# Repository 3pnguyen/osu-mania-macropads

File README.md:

# osu-mania-macropads 

## A repository that combines two seperate projects of similar design intentions but different executions.

<div align="center">
    <table>
        <tr>
            <td></td>
            <td></td>
        </tr>
    </table>
</div>

## ✨ About

At the start of the summer of 26' and as an osu! mania player, I started to develop a specialized macropad/keypad to play the game. Thinking of it as a quick and minimalistic project, that was the way I designed it. Minimalistic as in straight-up only a microcontroller and switches slapped onto a PCB. With only a total of 3 days working time, I finished it and thought it would be the end. But, my friend discovering the project, asked me to make a more "hardcore" version. Compared to the first version, we're talking about a potential of 9K mania, hall-effect switches, rapid trigger, etc. Orignally for the initial version, this repository has been repurposed to hold both. These two are brothers in arms, designed for different people with different demands but no less can be compiled together.

## 🖼️ Gallery

<div align="center">
    <table>
        <tr>
            <td></td>
            <td></td>
        </tr>
        <tr>
            <td></td>
            <td></td>
        </tr>
    </table>
</div>

<div align="center">
    <table>
        <tr>
            <td></td>
            <td></td>
        </tr>
    </table>
</div>

<div align="center">
    <table>
        <tr>
            <td></td>
            <td></td>
        </tr>
    </table>
</div>

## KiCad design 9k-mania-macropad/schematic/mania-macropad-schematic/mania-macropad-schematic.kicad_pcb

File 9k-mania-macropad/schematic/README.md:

# Schematic

<div align="center">

</div>

## Parts List

* [0.1uf](https://www.mouser.com/en/ProductDetail/KEMET/C322C104K5R5TA?qs=XvIqZs20p47gvrtGJkxvnw%3D%3D&srsltid=AfmBOoqY4KrbQpnZ-huLh4W_OdS7XR-RYfdhxsaF2TdTgfn78qcFuNxP)
* [10uf](https://www.mouser.com/en/ProductDetail/KEMET/C320C106K3R5TA?qs=uSb533yqMR%252BI5DZ88AMWgA%3D%3D&srsltid=AfmBOorKWxTFM7sGESwl3Y5iid5M9OMpDOqWwjicTUXBzjN7W4jSN1yL)
* [3.3k](https://www.mouser.com/en/ProductDetail/Vishay-Dale/RN55C3301FB14?qs=S3NOsHn6j1POW9KhX3p6iw%3D%3D)
* [4.7k](https://www.mouser.com/en/ProductDetail/Vishay-Dale/RN55C4701FB14?qs=iv4S7zUmpfIvlpqX3oroLw%3D%3D)
* [A1324LLHLT-T (Hall effect SOT-23-3)](https://www.mouser.com/en/ProductDetail/Allegro-MicroSystems/A1324LLHLT-T?qs=pUKx8fyJudDKEne7imXs%252BA%3D%3D)
* [971050321 (M3 5mm M-F Standoff)](https://www.mouser.com/en/ProductDetail/Wurth-Elektronik/971050321?qs=wr8lucFkNMVovcsNMvdJcg%3D%3D)|
* [M3 Screw](https://www.mouser.com/en/ProductDetail/APM-HEXSEAL/SM3X6MM-2701?qs=EY%2FnVpK1mpyaLaNu%2BOcvfQ%3D%3D)
* [M3 Nut](https://www.mouser.com/en/ProductDetail/Harwin/KA1-4300000?qs=HoCaDK9Nz5fHqS%2FcIXdxOA%3D%3D)
* [Teensy 4.0](https://www.mouser.com/en/ProductDetail/SparkFun/DEV-16997?qs=hWgE7mdIu5T2C4RvZCDz%2FQ%3D%3D)
* 6mm Push button - from local electronics store
* D5mm LED - from a random Arduino starter kit

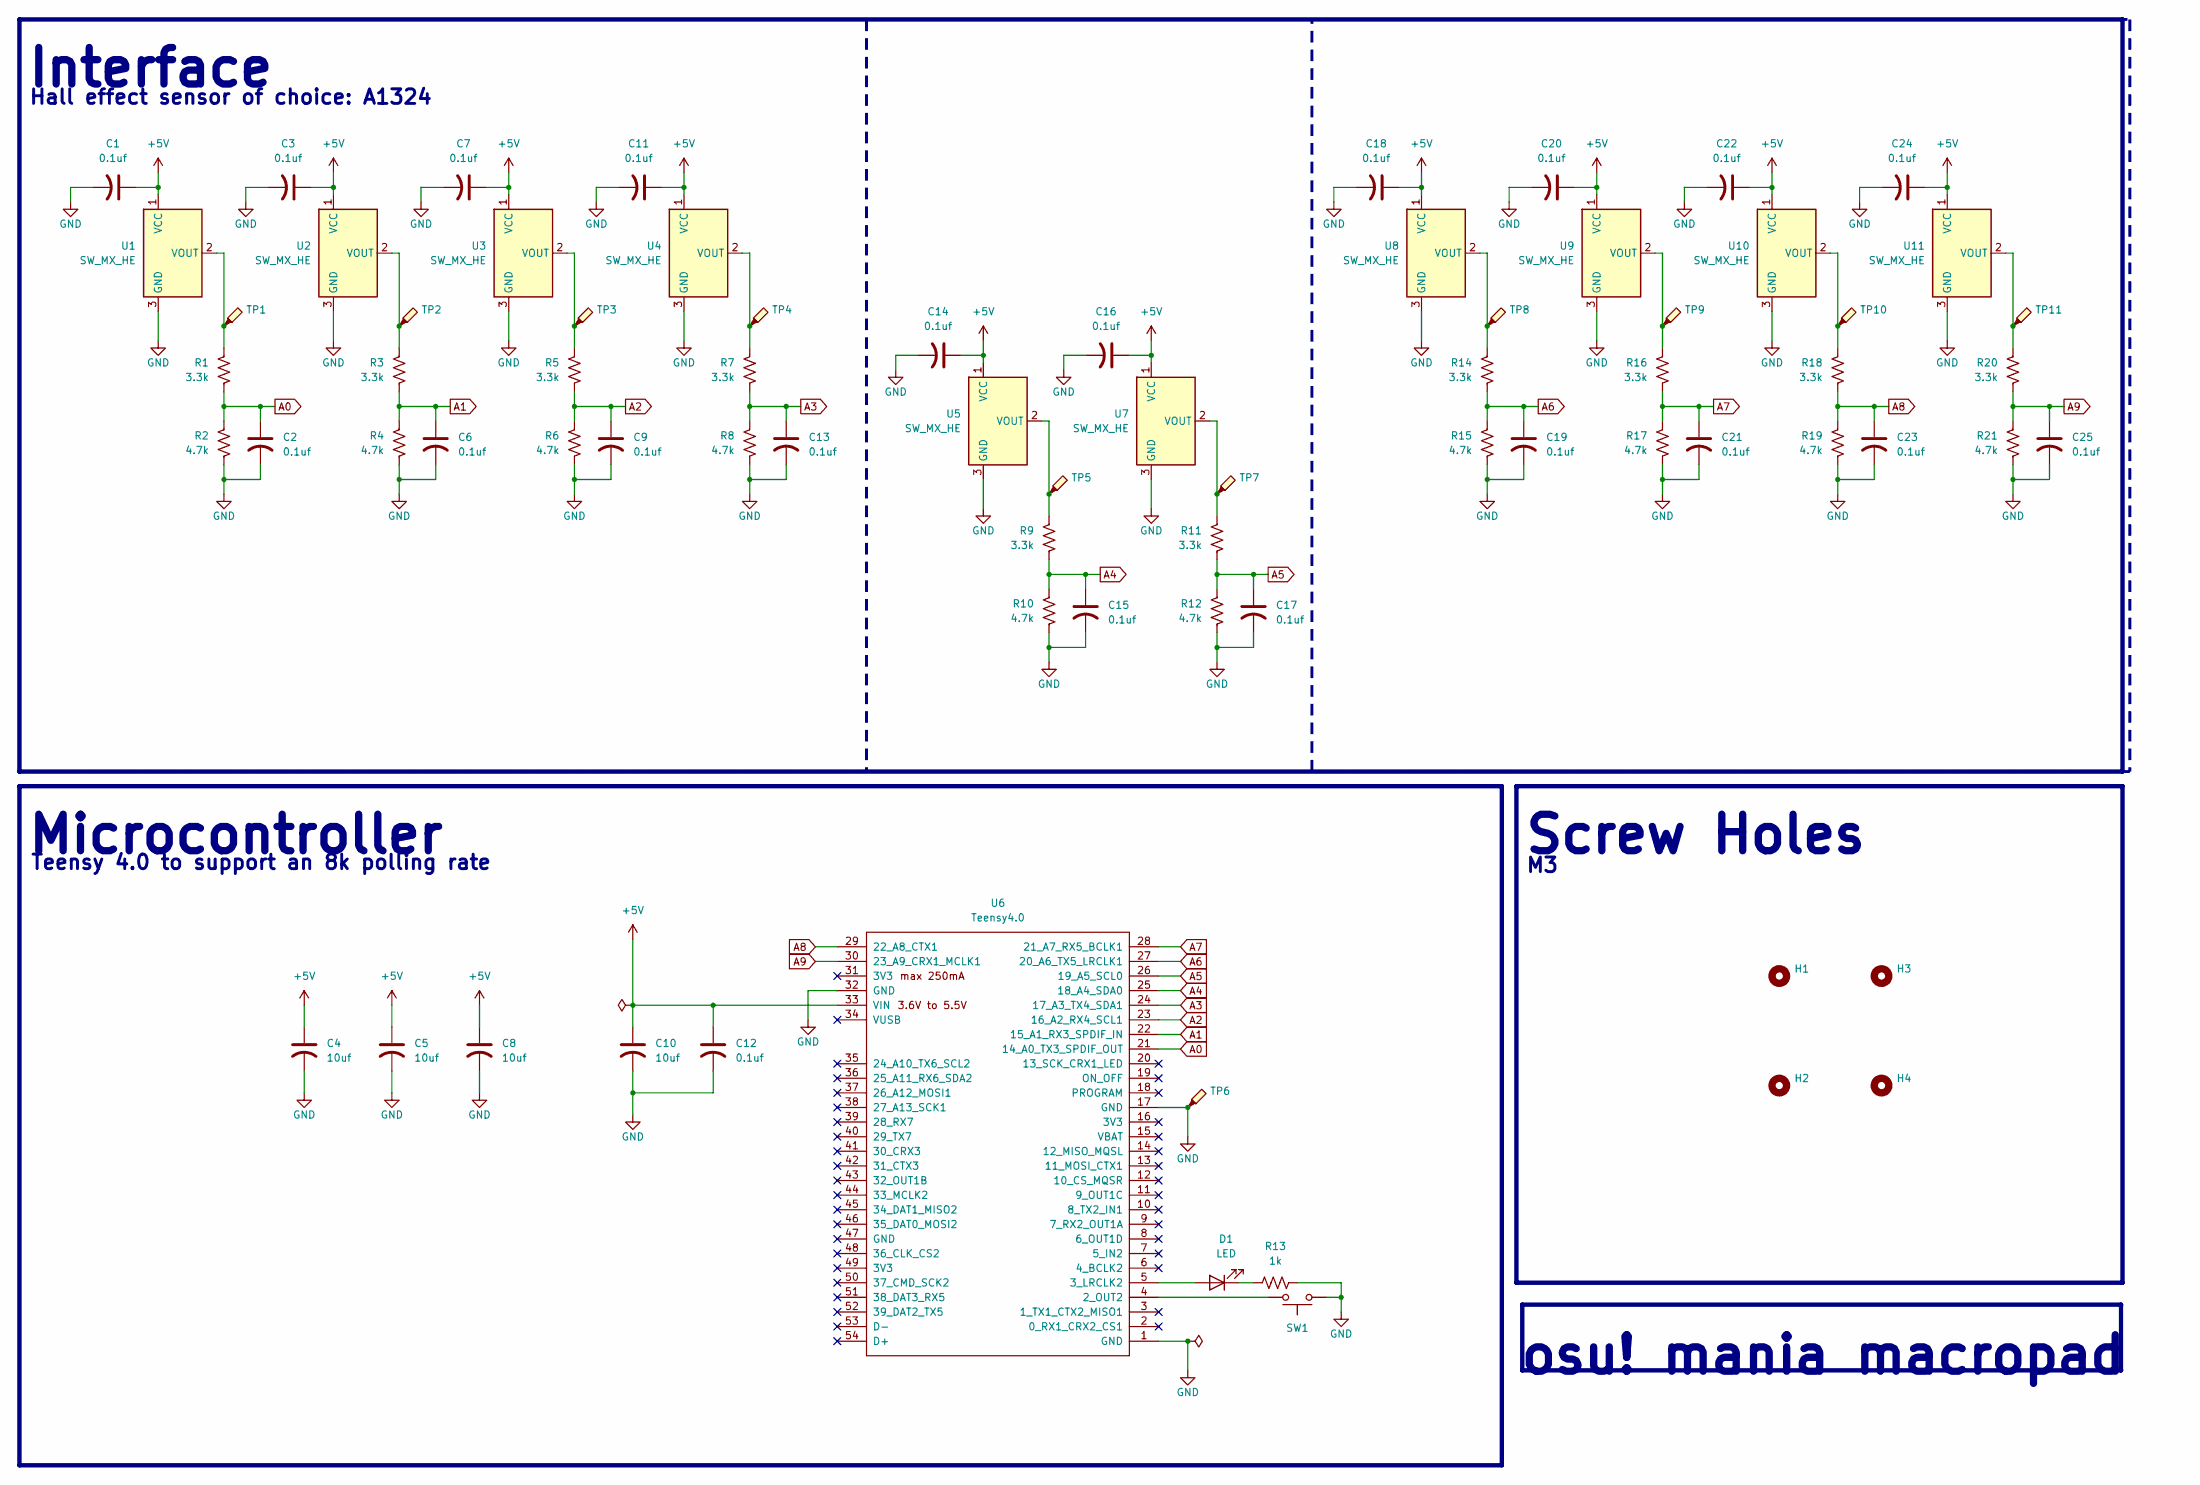
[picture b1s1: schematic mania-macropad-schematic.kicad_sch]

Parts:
C1, C2, C3, C6, C7, C9, C11, C12, C13, C14, C15, C16, C17, C18, C19, C20, C21, C22, C23, C24, C25: 0.1uf; C_Disc_D5.1mm_W3.2mm_P5.00mm
C4, C5, C8, C10: 10uf; C_Disc_D5.0mm_W2.5mm_P2.50mm
D1: LED; LED_D5.0mm
H1, H2, H3, H4: MountingHole; MountingHole_3.2mm_M3
R1, R3, R5, R7, R9, R11, R14, R16, R18, R20: 3.3k; R_Axial_DIN0207_L6.3mm_D2.5mm_P10.16mm_Horizontal
R2, R4, R6, R8, R10, R12, R15, R17, R19, R21: 4.7k; R_Axial_DIN0207_L6.3mm_D2.5mm_P10.16mm_Horizontal
R13: 1k; R_Axial_DIN0309_L9.0mm_D3.2mm_P12.70mm_Horizontal
SW1: SW_Push; SW_PUSH_6mm_H7.3mm
TP1, TP2, TP3, TP4, TP5, TP6, TP7, TP8, TP9, TP10, TP11: TestPoint_Probe; TestPoint_Pad_D1.5mm
U1, U2, U3, U4, U5, U7, U8, U9, U10, U11: SW_MX_HE; SW_MX_HE_0deg_1u
U6: Teensy4.0; Teensy40

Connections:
+5V: C1.1, C3.1, C4.1, C5.1, C7.1, C8.1, C10.1, C11.1, C12.1, C14.1, C16.1, C18.1, C20.1, C22.1, C24.1, U1.1 (VCC), U2.1 (VCC), U3.1 (VCC), U4.1 (VCC), U5.1 (VCC), U6.33 (VIN), U7.1 (VCC), U8.1 (VCC), U9.1 (VCC), U10.1 (VCC), U11.1 (VCC)
A0: C2.1, R1.2, R2.1, U6.21 (14_A0_TX3_SPDIF_OUT)
A1: C6.1, R3.2, R4.1, U6.22 (15_A1_RX3_SPDIF_IN)
A2: C9.1, R5.2, R6.1, U6.23 (16_A2_RX4_SCL1)
A3: C13.1, R7.2, R8.1, U6.24 (17_A3_TX4_SDA1)
A4: C15.1, R9.2, R10.1, U6.25 (18_A4_SDA0)
A5: C17.1, R11.2, R12.1, U6.26 (19_A5_SCL0)
A6: C19.1, R14.2, R15.1, U6.27 (20_A6_TX5_LRCLK1)
A7: C21.1, R16.2, R17.1, U6.28 (21_A7_RX5_BCLK1)
A8: C23.1, R18.2, R19.1, U6.29 (22_A8_CTX1)
A9: C25.1, R20.2, R21.1, U6.30 (23_A9_CRX1_MCLK1)
GND: C1.2, C2.2, C3.2, C4.2, C5.2, C6.2, C7.2, C8.2, C9.2, C10.2, C11.2, C12.2, C13.2, C14.2, C15.2, C16.2, C17.2, C18.2, C19.2, C20.2, C21.2, C22.2, C23.2, C24.2, C25.2, R2.2, R4.2, R6.2, R8.2, R10.2, R12.2, R13.2, R15.2, R17.2, R19.2, R21.2, SW1.2, TP6.1 (1_1), U1.3 (GND), U2.3 (GND), U3.3 (GND), U4.3 (GND), U5.3 (GND), U6.1 (GND), U6.17 (GND), U6.32 (GND), U7.3 (GND), U8.3 (GND), U9.3 (GND), U10.3 (GND), U11.3 (GND)
unnamed: D1.2 (A), U6.5 (3_LRCLK2)
unnamed: D1.1 (K), R13.1
unnamed: R1.1, TP1.1 (1_1), U1.2 (VOUT)
unnamed: R3.1, TP2.1 (1_1), U2.2 (VOUT)
unnamed: R5.1, TP3.1 (1_1), U3.2 (VOUT)
unnamed: R7.1, TP4.1 (1_1), U4.2 (VOUT)
unnamed: R9.1, TP5.1 (1_1), U5.2 (VOUT)
unnamed: SW1.1, U6.4 (2_OUT2)
unnamed: R11.1, TP7.1 (1_1), U7.2 (VOUT)
unnamed: R14.1, TP8.1 (1_1), U8.2 (VOUT)
unnamed: R16.1, TP9.1 (1_1), U9.2 (VOUT)
unnamed: R18.1, TP10.1 (1_1), U10.2 (VOUT)
unnamed: R20.1, TP11.1 (1_1), U11.2 (VOUT)

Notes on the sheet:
Screw Holes
Teensy 4.0 to support an 8k polling rate
Microcontroller
Hall effect sensor of choice: A1324
Interface
osu! mania macropad

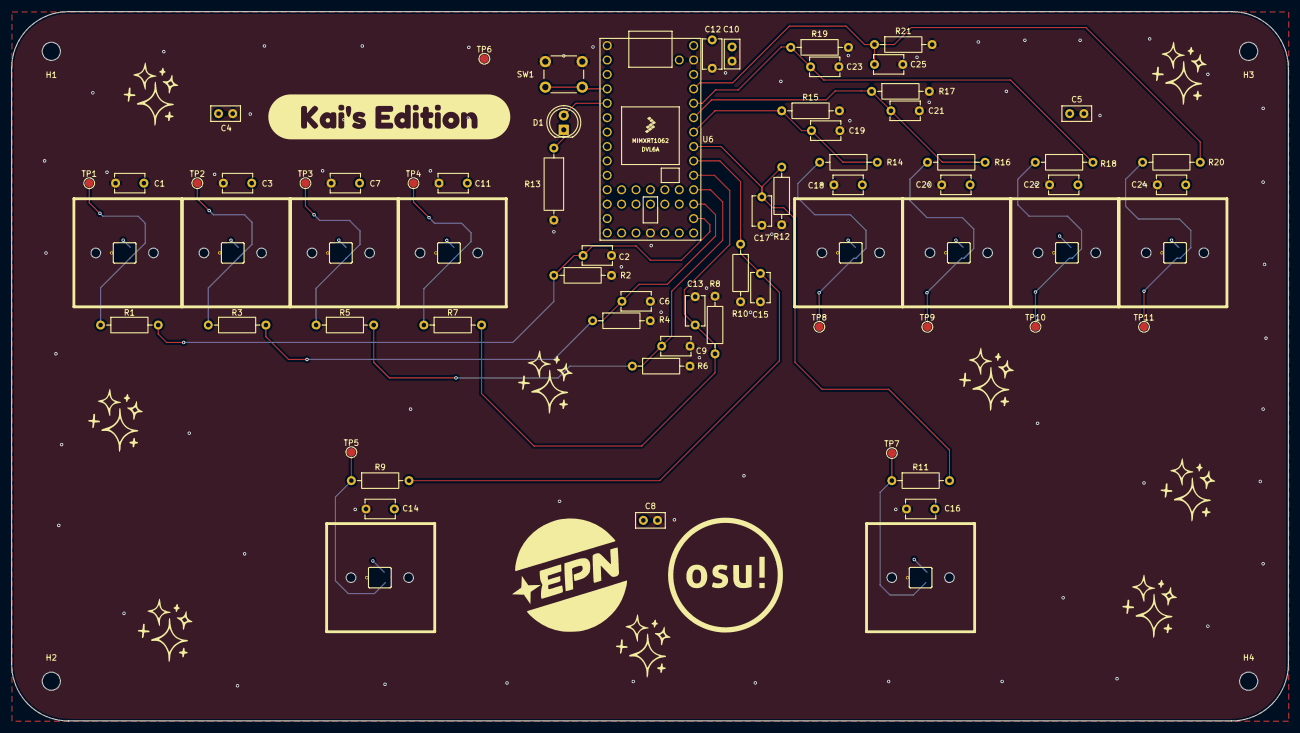
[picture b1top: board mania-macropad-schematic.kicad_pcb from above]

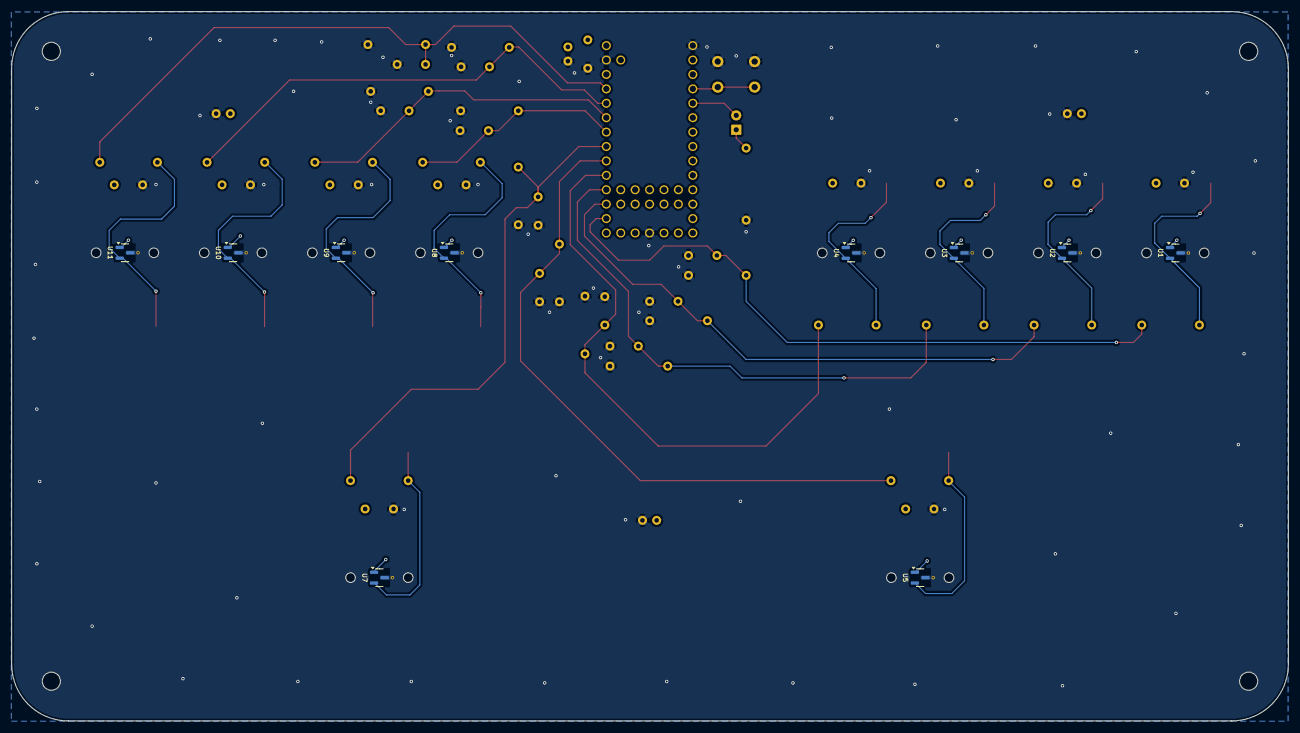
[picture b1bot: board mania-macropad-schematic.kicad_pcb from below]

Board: 4 copper layers, 225.0 x 125.0 mm, 75 parts (10 on the bottom side), 25 nets.

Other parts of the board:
kibuzzard-6A6824D3: G***; kibuzzard-6A6824D3

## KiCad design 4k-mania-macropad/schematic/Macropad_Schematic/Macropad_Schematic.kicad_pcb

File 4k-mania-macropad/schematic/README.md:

# Schematic

Very simple with only a few switches connected to some GPIO on the MCU + some mounting holes for structure and support

<div align="center">

</div>

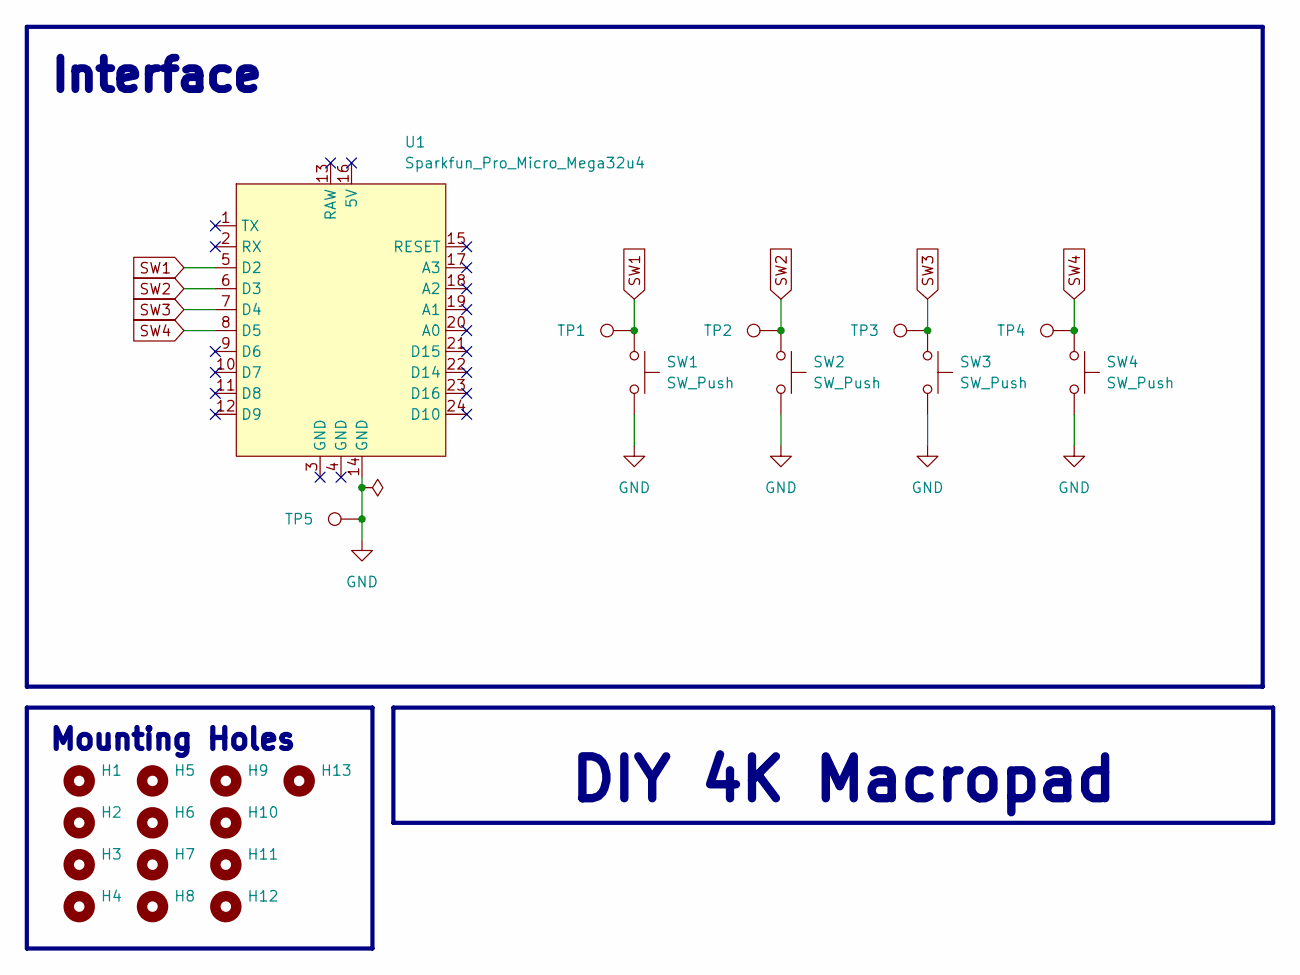
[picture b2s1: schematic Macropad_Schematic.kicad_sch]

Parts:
H1, H2, H3, H4, H5, H6, H7, H8, H9, H10, H11, H12, H13: MountingHole; MountingHole_3.2mm_M3
SW1, SW2, SW3, SW4: SW_Push; SW_choc_v2_1u
TP1, TP2, TP3, TP4, TP5: TestPoint; TestPoint_Pad_D2.5mm
U1: Sparkfun_Pro_Micro_Mega32u4; ProMicro

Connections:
GND: SW1.2, SW2.2, SW3.2, SW4.2, TP5.1 (1_1), U1.14 (GND)
SW1: SW1.1, TP1.1 (1_1), U1.5 (D2)
SW2: SW2.1, TP2.1 (1_1), U1.6 (D3)
SW3: SW3.1, TP3.1 (1_1), U1.7 (D4)
SW4: SW4.1, TP4.1 (1_1), U1.8 (D5)

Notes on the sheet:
Interface
DIY 4K Macropad
Mounting Holes

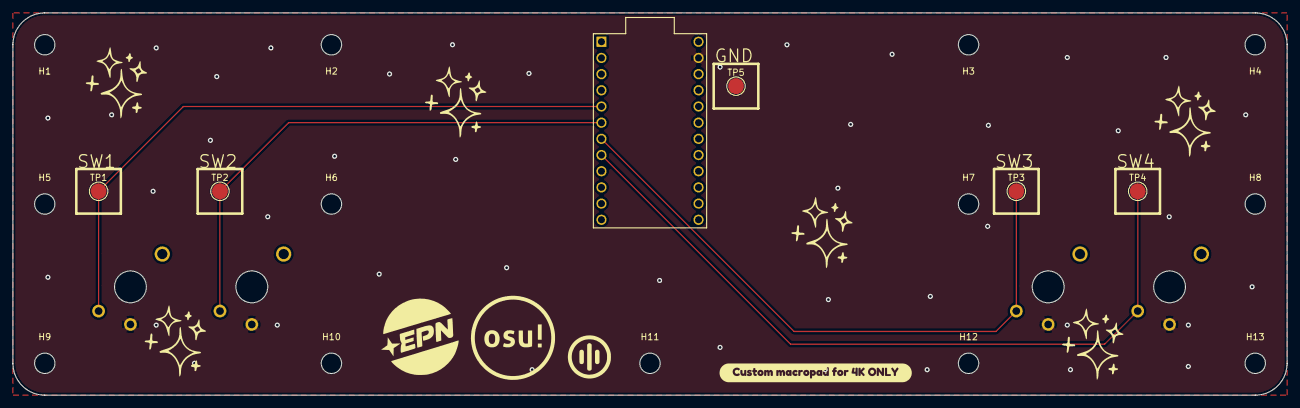
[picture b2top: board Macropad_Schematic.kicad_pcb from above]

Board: 2 copper layers, 200.0 x 60.0 mm, 24 parts (0 on the bottom side), 5 nets.

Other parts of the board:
kibuzzard-6A484497: G***; kibuzzard-6A484497
